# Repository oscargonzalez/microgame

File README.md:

MicroGame - Custom Arduino Compatible Gamming Platform
======================================================

The MicroGame is an experiment of making a custom portable platform for gamming compatible with Arduino. It's based on a small monochrome 128x64 pixels OLED from Adafruit and a ATmega32U40 8-bits microcontroller running at 8MHz.
All hardware design and game source code is writed from scratch and you can find all the file sin this repository if you want to build your own. You can modify, share and make improvements as you like but do not forget to shoot me and email and show me your work!

First blog post:
http://blog.bricogeek.com/noticias/electronica/microgame-consola-de-juego-casera-basada-en-arduino/

Final proyect post:
http://blog.bricogeek.com/noticias/arduino/microgame-consola-de-juego-compatible-con-arduino-proyecto-final/

Oscar Gonzalez August 2014 - January 2015
www.bricogeek.com

Repository Contents
-------------------
* **/USB driver** - USB driver (tested on Win 7 64-bits). Identifies as Sparkfun Pro Micro 3.3V @ 8MHz
* **/datasheet** - Various datasheets for reference
* **/eagle files** - Eagle design files of the board (schematic and PCB)
* **/src** - Source files for the game for at least Arduino IDE 1.0

License Information
-------------------
The hardware is released under [Creative Commons Share-alike 3.0](http://creativecommons.org/licenses/by-sa/3.0/).  
All other code is open source so please feel free to do anything you want with it; you buy me a beer if you use this and we meet someday ([Beerware license](http://en.wikipedia.org/wiki/Beerware)).

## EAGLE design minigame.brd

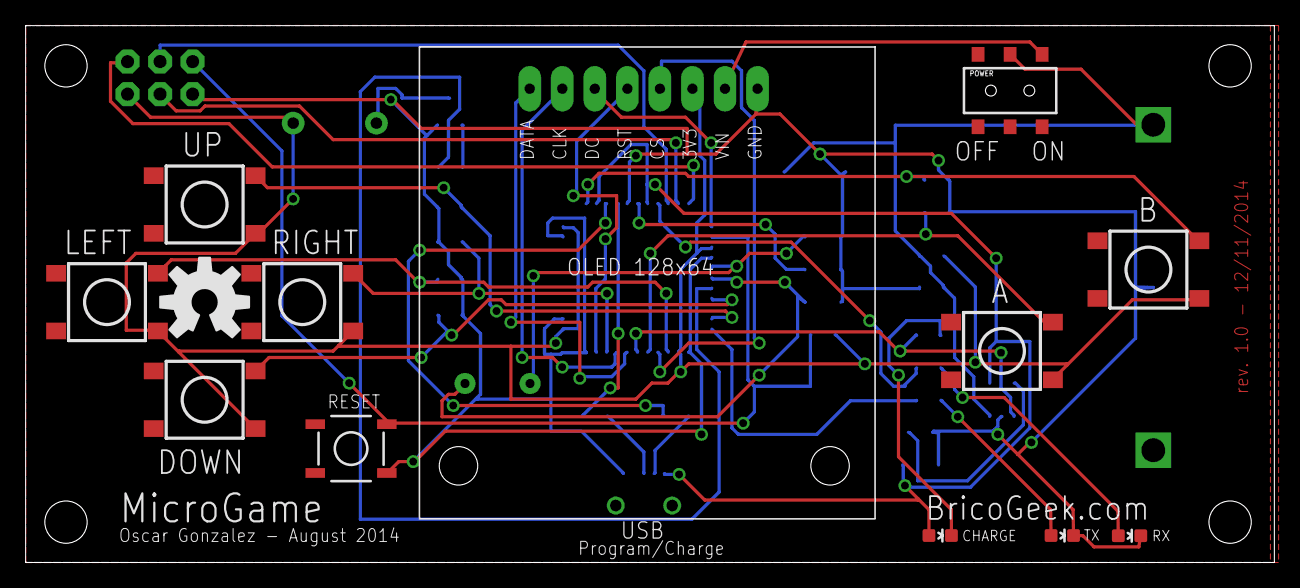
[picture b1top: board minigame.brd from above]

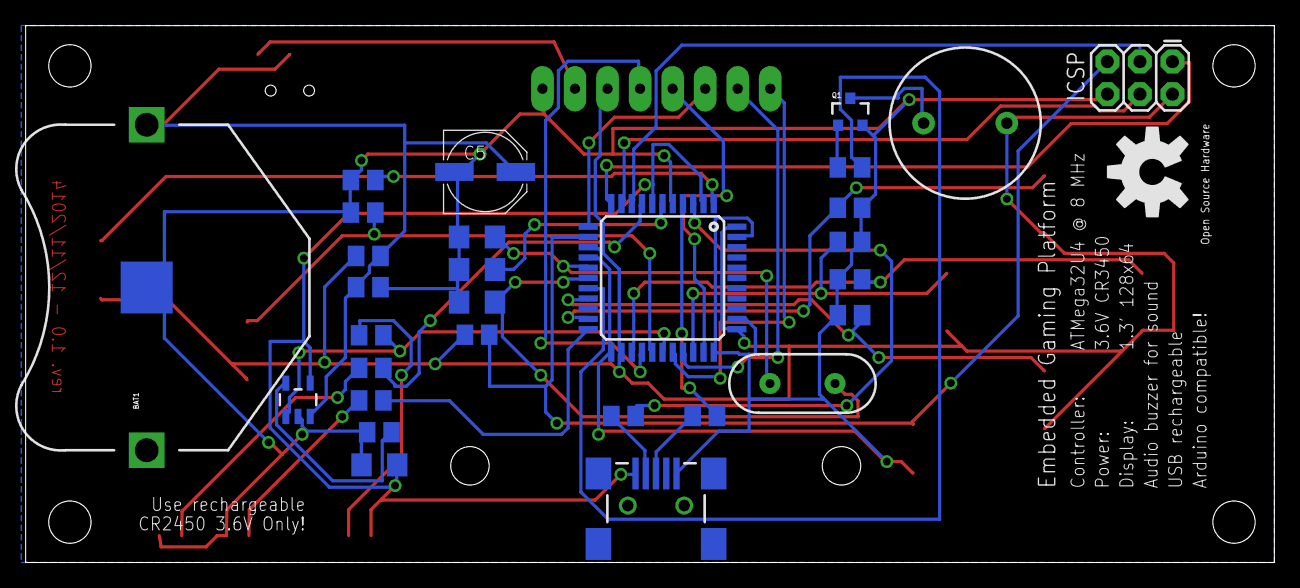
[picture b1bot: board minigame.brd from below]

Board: 2 copper layers, 97.5 x 41.9 mm, 47 parts (30 on the bottom side), 37 nets.

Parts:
BAT1: 3.6V-PRT-10319; BATTCON_245MM_PTH
C1, C2: 22pF; 1206
C3: 1uF; 1206
C4: 4.7uF; 1206
C5: 10uF; PANASONIC_D
ICSP: AVR_SPI_PRG_6PTH; 2X3
JP1: USB-SMD-NS; USB-MINIB-NOSTOP
LED1: RED; LED-0603
LED2: YELLOW; LED-0603
LED3: BLUE; LED-0603
OLED128X64: OLED128X64-ADAFRUIT938; 938
POWER: ON/OFF; AYZ0202
Q1: MMBT2222A; SOT23-3
R1, R4, R5, R6, R7, R8, R9, R15, R16: 10k; M0805
R2, R3: 22; M0805
R10: 30k; M0805
R11: 470; M0805
R12: 180; M0805
R13, R14: 330; M0805
S1: RESET; TACTILE-SWITCH-SMD
S2: DOWN; TACTILE_SWITCH_TALL
S3: LEFT; TACTILE_SWITCH_TALL
S4: RIGHT; TACTILE_SWITCH_TALL
S5: A; TACTILE_SWITCH_TALL
S6: B; TACTILE_SWITCH_TALL
S9: UP; TACTILE_SWITCH_TALL
SG1: BUZZERPTH; BUZZER-12MM
U1: MCP73831; SOT23-5
U$1: ATMEGA32U4TQFP-44; TQFP44
U$2, U$4, U$5, U$6: STAND-OFF
U$3, U$7: OSHW-LOGO-L
Y1: 8MHz; HC49US

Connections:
3.3V: ICSP.2, OLED128X64.3V3, R1.2, R15.1, S2.A2, S3.A2, S4.A2, S5.A2, S6.A2, S9.A2, SG1.+, U$1.14, U$1.24, U$1.34, U$1.44
A: R8.2, S5.B2, U$1.27
B: R9.2, S6.B2, U$1.1
BUZZER: R12.2, U$1.18
CHARGE: R11.1, U1.1, U$1.28
D+: R3.1, U$1.4
D-: R2.1, U$1.3
DOWN: R5.2, S2.B2, U$1.19
GND: BAT1.2, C1.1, C2.1, C3.1, C4.1, C5.-, ICSP.6, JP1.GND, LED2.C, LED3.C, OLED128X64.GND, Q1.2, R4.1, R5.1, R6.1, R7.1, R8.1, R9.1, R10.2, R16.2, S1.1, U1.2, U$1.5, U$1.15, U$1.23, U$1.33, U$1.35, U$1.43
LEFT: R6.2, S3.B2, U$1.25
MISO: ICSP.1, U$1.11
MOSI: ICSP.4, U$1.10
unnamed: C1.2, U$1.17, Y1.2
unnamed: C2.2, U$1.16, Y1.1
unnamed: Q1.3, SG1.-
unnamed: JP1.D-, R2.2
unnamed: JP1.D+, R3.2
unnamed: C3.2, U$1.6
unnamed: R10.1, U1.5
unnamed: LED1.C, R11.2
unnamed: Q1.1, R12.1
unnamed: LED2.A, R13.2
unnamed: LED3.A, R14.2
unnamed: R13.1, U$1.22
unnamed: R14.1, U$1.8
OLED_CLK: OLED128X64.CLK, U$1.30
OLED_CS: OLED128X64.CS, U$1.26
OLED_DATA: OLED128X64.DATA, U$1.29
OLED_DC: OLED128X64.DC, U$1.12
OLED_RST: OLED128X64.RST, U$1.32
POWER: OLED128X64.VIN, POWER.3
RIGHT: R7.2, S4.B2, U$1.31
RST: ICSP.5, R1.1, S1.3, U$1.13
SCK: ICSP.3, U$1.9
UP: R4.2, S9.B2, U$1.21
VBAT: BAT1.3, C5.+, POWER.2, R15.2, R16.1, U1.3
VBUS: C4.2, JP1.VBUS, LED1.A, U1.4, U$1.2, U$1.7

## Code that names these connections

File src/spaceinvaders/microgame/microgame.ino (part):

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
// Uncomment this block to use hardware SPI (MUCH faster but not supported in hardware yet, sorry!)
/*
#define OLED_DC     6
#define OLED_CS     7
#define OLED_RESET  8
Adafruit_SSD1306 display(OLED_DC, OLED_RESET, OLED_CS);
*/

// Software SPI (SLOWER!)
#define OLED_MOSI   9
#define OLED_CLK   10
#define OLED_DC    11
#define OLED_CS    12
#define OLED_RESET 13
Adafruit_SSD1306 display(OLED_MOSI, OLED_CLK, OLED_DC, OLED_RESET, OLED_CS);

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
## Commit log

2014-07-21 Added regulador and charger circuit
2014-07-22 Vista preliminar de la placa (BRD)
2014-07-22 Added gitignore Removed Eagle temp files and added to gitignore
2014-07-22 Added OLED wires Added buzzer circuit
2014-07-22 Added RX/TX LEDs
2014-07-24 Added OLED border in BRD
2014-07-24 Preliminary components placement
2014-07-24 board
2014-07-25 Board placement
2014-07-25 Added Arduino code and some sprites!
2014-07-26 Starfield fix (too slow!)
2014-07-26 Added some functions and test movement pattern for batteship
2014-07-26 starfield fix
2014-07-27 Updated sprites New enemys!(5 in total) Fixed starfield. Now in panoramic mode (right to left) Some defines for finetuning
2014-07-27 Fire routine done!
2014-07-27 New class Enemy
2014-07-27 Clean
2014-07-27 Enemy class functions
2014-07-28 Enemy animation loop (some slow sine and cosine funtions...)
2014-07-28 Collision class and first test
2014-07-28 Added enemy explosion sprite (5 frames)
2014-07-29 Added holes and dimensions
2014-07-29 Holes fix
2014-08-01 Now using hardware SPI(must faster!) with Sparkfun ProMicro 3.3V @8MHz
2014-08-01 Added FPS counter over serial.
2014-08-01 Test font function (not working)
2014-08-01 Enemy fix
2014-08-07 Added button controls
2014-08-07 New class controls (unfinished but working)
2014-08-07 Batteship moves
2014-08-07 fix controls with array
2014-08-07 test playtune
2014-08-13 Removed Playtune
2014-08-13 Removed redraw to black. Now uses clearDisplay Some variable type changes
2014-08-13 Enemy epplosion on dead!
2014-08-13 Display score Fix battleship first position
2014-08-13 Display score and lives
2014-08-13 Batteship to Alien colision decrease lives.
2014-08-13 Added some crappy sound!
2014-08-13 gameover function (tofix)
2014-10-05 Ajuste en PCB
2014-10-16 Ripup board layout
2014-10-16 Voltage regulator removed Preliminary Routing test
2014-11-12 Added new custom package for OLED display Updated schematic
2014-11-12 Board 100% routed!
2014-11-12 Ground plane in top and bottom
2014-11-12 Added some stuff to board layout and cleaning
2015-01-19 Added datasheets Added USB driver (Win 7 32/64bits) Added original Sparkfun Pro Micro reference files and docs Moved Eagle files
2015-01-19 Changed directory name for microgame source Fix pin assignment for software SPI (ouch!)
2015-01-20 Some game fixes and gameover screen.
2015-01-20 Little fixes in game and updated readme
2015-02-06 Readme update
    Added blog post for more information

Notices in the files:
parts and their libraries:
SparkFun-Electromechanical: Licensing: Creative Commons ShareAlike 4.0 International - https://creativecommons.org/licenses/by-sa/4.0
